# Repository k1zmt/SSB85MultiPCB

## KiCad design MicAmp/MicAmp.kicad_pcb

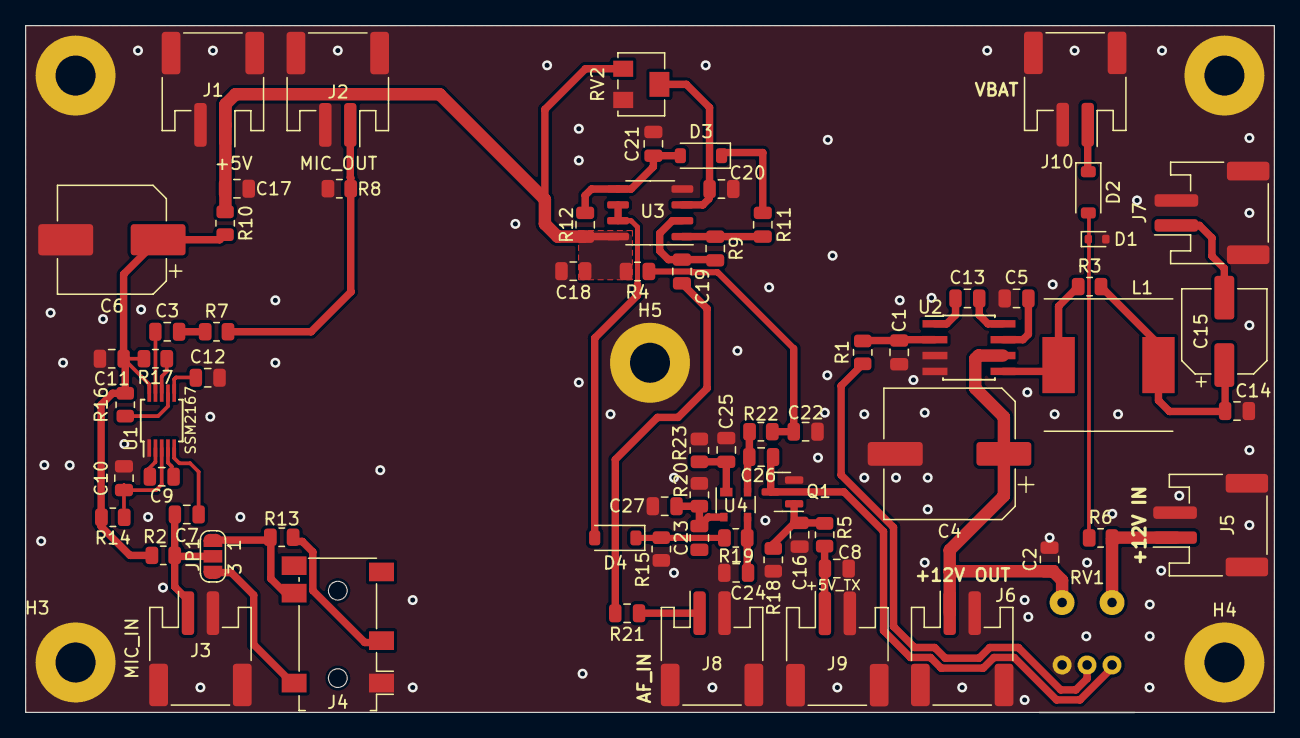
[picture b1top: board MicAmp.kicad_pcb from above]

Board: 2 copper layers, 100.0 x 55.0 mm, 78 parts (0 on the bottom side), 46 nets.

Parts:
C1: 222; C_0805_2012Metric
C2, C3, C5, C9, C12, C13, C22, C25, C26: 106; C_0805_2012Metric
C4: 1000uFx16V; CP_Elec_10x12.6
C6: 100uFx6.3V; CP_Elec_8x10.5
C7, C8, C10, C11, C16, C17, C18, C19, C20, C24, C27: 104; C_0805_2012Metric
C14: 473; C_0805_2012Metric
C15: 227; CP_Elec_6.3x3
C21, C23: 105; C_0805_2012Metric
D1: DZ2S036X0L; D_SOD-523
D2: 1N4148; D_SOD-123
D3, D4: MBR0520; D_SOD-123
H1, H2, H3, H4, H5: MH; MountingHole_3.2mm_M3_Pad
J1: +5V; JST_PH_S2B-PH-SM4-TB_1x02-1MP_P2.00mm_Horizontal
J2: MIC_OUT; JST_PH_S2B-PH-SM4-TB_1x02-1MP_P2.00mm_Horizontal
J3: MIC_IN; JST_PH_S2B-PH-SM4-TB_1x02-1MP_P2.00mm_Horizontal
J4: AudioJack3_Ground_SwitchTR; Jack_3.5mm_PJ342_Horizontal2
J5: +12V IN; JST_PH_S2B-PH-SM4-TB_1x02-1MP_P2.00mm_Horizontal
J6: +12V OUT; JST_PH_S2B-PH-SM4-TB_1x02-1MP_P2.00mm_Horizontal
J7: SPEAKER; JST_PH_S2B-PH-SM4-TB_1x02-1MP_P2.00mm_Horizontal
J8: AF_IN; JST_PH_S2B-PH-SM4-TB_1x02-1MP_P2.00mm_Horizontal
J9: +5V_TX; JST_PH_S2B-PH-SM4-TB_1x02-1MP_P2.00mm_Horizontal
J10: VBAT; JST_PH_S2B-PH-SM4-TB_1x02-1MP_P2.00mm_Horizontal
JP1: MIC; SolderJumper-3_P1.3mm_Open_RoundedPad1.0x1.5mm_NumberLabels
L1: L_Ferrite; L_Taiyo-Yuden_NR-10050_9.8x10.0mm
Q1: BSS123; SOT-23
R1, R2, R5, R14, R15, R18, R19: 103; R_0805_2012Metric
R3, R10: 47R; R_0805_2012Metric
R4: 510; R_0805_2012Metric
R6: 106; R_0805_2012Metric
R7, R8: 472; R_0805_2012Metric
R9: 104; C_0805_2012Metric
R11, R21: 102; C_0805_2012Metric
R12: 105; C_0805_2012Metric
R13, R20: 101; R_0805_2012Metric
R16: 202; R_0805_2012Metric
R17: 473; R_0805_2012Metric
R22: 681; R_0805_2012Metric
R23: 221; R_0805_2012Metric
RV1: A10K; Potentiometer_Switch
RV2: 503; Potentiometer_Bourns_3224W_Vertical
U1: SSM2167; MSOP-10_3x3mm_P0.5mm
U2: LM386; PowerIntegrations_SO-8
U3: LM358; SO-8_3.9x4.9mm_P1.27mm
U4: BF998R; SOT-143R

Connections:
+5V: C17.1, C18.2, J1.1, R4.2, R10.1, R12.2, RV2.1, U3.8 (V+)
+12V: C2.2, C4.1, J6.1, RV1.5 (S1), U2.6 (V+)
/+5V_MIC_COMP: C6.1, C11.1, R2.1, R10.2, R14.2, R16.1, R17.1, U1.10 (V+)
/+12V_IN: J5.1, R6.2, RV1.4 (S2)
/AF_AGC_OUT: C26.2, Q1.3 (D), RV1.3
/AUDIO_IN: C23.1, J8.1, R21.1
/MIC: C7.2, J3.1, JP1.2 (C), R2.2
/MIC_OUT: J2.1, R7.2, R8.2
/SPK: C15.2, J7.1
/VBAT: D2.1 (K), J10.1
Earth: C1.2, C2.1, C4.2, C5.1, C6.2, C8.2, C10.1, C11.2, C12.2, C14.2, C16.2, C17.2, C18.1, C20.1, C21.1, C22.1, C24.1, C25.1, C27.1, D1.2 (A), H1.1, H2.1, H3.1, H4.1, H5.1, J1.2, J1.MP (MountPin), J2.2, J2.MP (MountPin), J3.2, J3.MP (MountPin), J4.G, J5.2, J5.MP (MountPin), J6.2, J6.MP (MountPin), J7.2, J7.MP (MountPin), J8.2, J8.MP (MountPin), J9.2, J9.MP (MountPin), J10.2, J10.MP (MountPin), Q1.2 (S), R8.1, R15.2, R18.1, R20.2, R23.2, RV1.1, RV2.3, U1.1 (GND), U2.3 (+), U2.4 (GND), U3.4 (V-)
unnamed: C3.2, R7.1
unnamed: C13.1, U2.1 (GAIN)
unnamed: C13.2, U2.8 (GAIN)
unnamed: C14.1, C15.1, L1.2, R3.2
unnamed: C19.1, R21.2
unnamed: C22.2, R4.1, R22.1
unnamed: D1.1 (K), D2.2 (A), R6.1
unnamed: C21.2, D3.2 (A), R12.1, U3.5 (+)
unnamed: D3.1 (K), R11.2
unnamed: D4.2 (A), U3.6 (-), U3.7
unnamed: D4.1 (K), R15.1, R19.1
unnamed: J4.R, R13.1
unnamed: J4.T, JP1.1 (A), R13.2
unnamed: J4.S, JP1.3 (B)
unnamed: L1.1, R3.1, U2.5
unnamed: C16.1, Q1.1 (G), R5.2, R18.2
unnamed: R1.1, RV1.2
unnamed: R9.2, R11.1, U3.1
unnamed: C12.1, U1.6 (AVG)
unnamed: C9.1, U1.4 (BUFOUT)
unnamed: R17.2, U1.8 (COMP)
unnamed: R16.2, U1.7 (GATE)
unnamed: C7.1, U1.5 (IN+)
unnamed: C9.2, U1.2 (VCAIN)
unnamed: C3.1, U1.9 (VOUT)
unnamed: C10.2, R14.1, U1.3 (~SD)
unnamed: C1.1, R1.2, U2.2 (-)
unnamed: C5.2, U2.7 (BYPASS)
unnamed: C20.2, RV2.2, U3.3 (+)
unnamed: C19.2, R9.1, U3.2 (-)
unnamed: C26.1, R22.2, U4.2 (D)
unnamed: C23.2, C27.2, R20.1, U4.4 (G1)
unnamed: C24.2, R19.2, U4.3 (G2)
unnamed: C25.2, R23.1, U4.1 (S)
TX+5V: C8.1, J9.1, R5.1

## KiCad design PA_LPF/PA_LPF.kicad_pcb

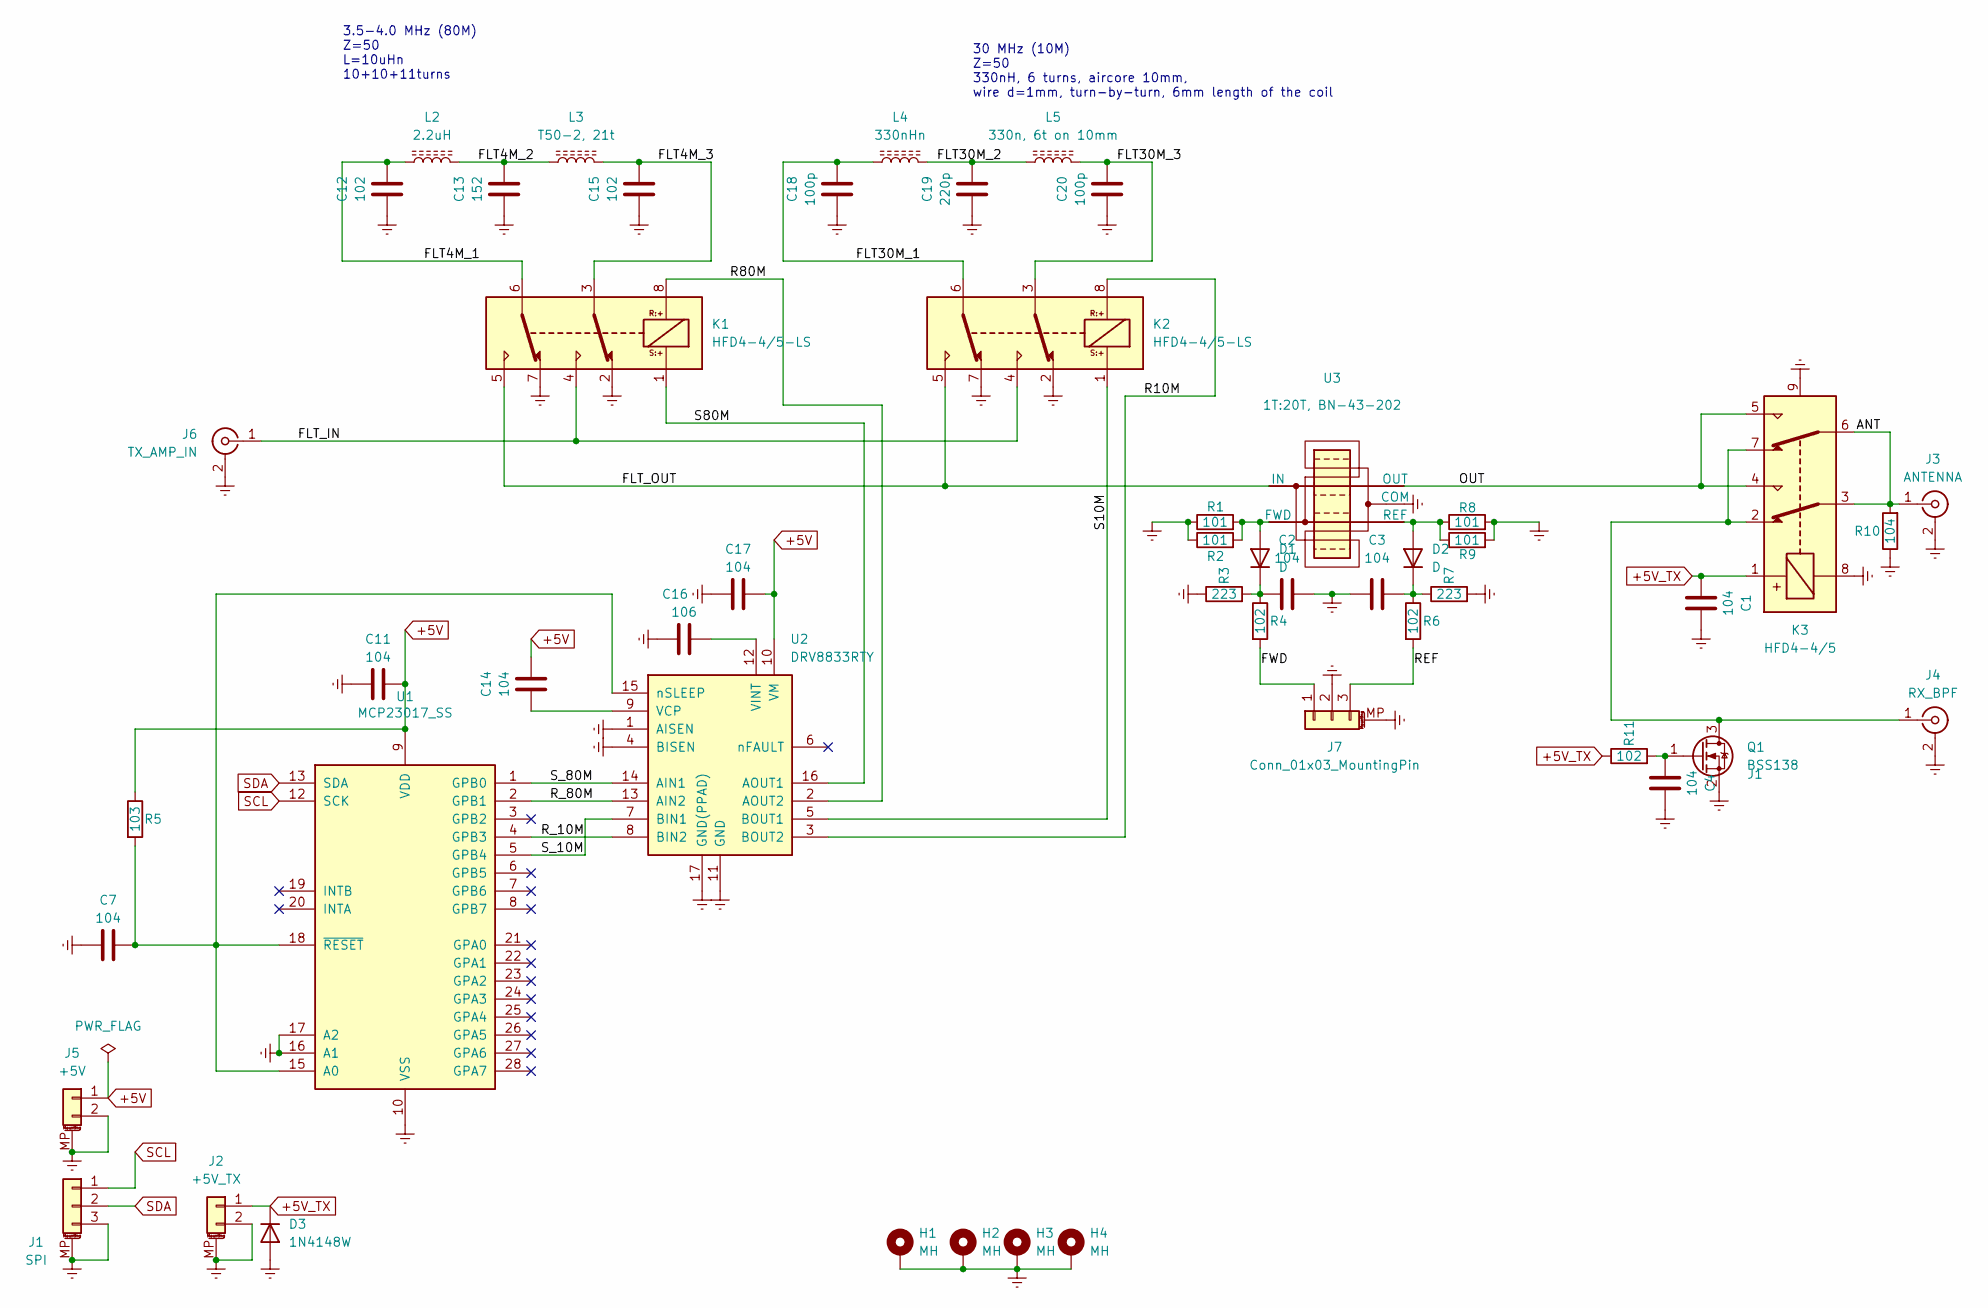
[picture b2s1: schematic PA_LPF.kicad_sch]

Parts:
C1, C2, C3, C4, C7, C11, C14, C17: 104; C_0805_2012Metric
C12, C15: 102; C_1206_3216Metric
C13: 152; C_1206_3216Metric
C16: 106; C_0805_2012Metric
C18, C20: 100p; C_1206_3216Metric
C19: 220p; C_1206_3216Metric
D1, D2: D; D_SOD-123
D3: 1N4148W; D_SOD-123
H1, H2, H3, H4: MH; MountingHole_3.2mm_M3_Pad
J1: SPI; JST_PH_S3B-PH-SM4-TB_1x03-1MP_P2.00mm_Horizontal
J2: +5V_TX; JST_PH_S2B-PH-SM4-TB_1x02-1MP_P2.00mm_Horizontal
J3: ANTENNA; SMA_Amphenol_132289_EdgeMount
J4: RX_BPF; SMA_Amphenol_132289_EdgeMount
J5: +5V; JST_PH_S2B-PH-SM4-TB_1x02-1MP_P2.00mm_Horizontal
J6: TX_AMP_IN; SMA_Samtec_SMA-J-P-X-ST-EM1_EdgeMount
J7: Conn_01x03_MountingPin; JST_PH_S3B-PH-SM4-TB_1x03-1MP_P2.00mm_Horizontal
K1, K2: HFD4-4/5-LS; Relay_DPDT_Omron_G6K-2F-Y
K3: HFD4-4/5; Relay_DPDT_Omron_G6K-2F-Y
L2: 2.2uH; L_T50_L13_W8_P5mm
L3: T50-2, 21t; L_T50_L13_W8_P5mm
L4: 330nHn; L_T50_L13_W8_P5mm
L5: 330n, 6t on 10mm; L_T50_L13_W8_P5mm
Q1: BSS138; SOT-23
R1, R2, R8, R9: 101; R_1812_4532Metric
R3, R7: 223; R_0805_2012Metric
R4, R6, R11: 102; R_0805_2012Metric
R5: 103; R_0805_2012Metric
R10: 104; R_0805_2012Metric
U1: MCP23017_SS; SSOP-28_5.3x10.2mm_P0.65mm
U2: DRV8833RTY; Texas_S-PWQFN-N16_EP2.1x2.1mm_ThermalVias
U3: 1T:20T, BN-43-202; Balun_5PIN_BN-43-202_SMD_SWR_Bridge

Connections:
+5V: C11.1, C14.2, C17.2, J5.1, R5.1, U1.9 (VDD), U2.10 (VM)
+5V_TX: C1.1, D3.1 (K), J2.1, K3.1, R11.1
/ANT: J3.1 (In), K3.3, K3.6, R10.2
/FLT4M_1: C12.2, K1.6, L2.1
/FLT4M_2: C13.2, L2.2, L3.1
/FLT4M_3: C15.2, K1.3, L3.2
/FLT30M_1: C18.2, K2.6, L4.1
/FLT30M_2: C19.2, L4.2, L5.1
/FLT30M_3: C20.2, K2.3, L5.2
/FLT_IN: J6.1 (In), K1.4, K2.4
/FLT_OUT: K1.5, K2.5, U3.1 (IN)
/FWD: J7.1, R4.2
/OUT: K3.4, K3.5, U3.2 (OUT)
/R10M: K2.8, U2.3 (BOUT2)
/R80M: K1.8, U2.2 (AOUT2)
/REF: J7.3, R6.2
/R_10M: U1.4 (GPB3), U2.8 (BIN2)
/R_80M: U1.2 (GPB1), U2.13 (AIN2)
/S10M: K2.1, U2.5 (BOUT1)
/S80M: K1.1, U2.16 (AOUT1)
/S_10M: U1.5 (GPB4), U2.7 (BIN1)
/S_80M: U1.1 (GPB0), U2.14 (AIN1)
Earth: C1.2, C2.2, C3.1, C4.2, C7.1, C11.2, C12.1, C13.1, C15.1, C16.1, C17.1, C18.1, C19.1, C20.1, D3.2 (A), H1.1, H2.1, H3.1, H4.1, J1.3, J1.MP (MountPin), J2.2, J2.MP (MountPin), J3.2 (Ext), J4.2 (Ext), J5.2, J5.MP (MountPin), J6.2 (Ext), J7.2, J7.MP (MountPin), K1.2, K1.7, K2.2, K2.7, K3.8, K3.9, Q1.2 (S), R1.1, R2.1, R3.1, R7.2, R8.2, R9.2, R10.1, U1.10 (VSS), U1.16 (A1), U1.17 (A2), U2.1 (AISEN), U2.4 (BISEN), U2.11 (GND), U2.17 (GND(PPAD)), U3.3 (COM)
unnamed: D1.2 (A), R1.2, R2.2, U3.5 (FWD)
unnamed: C2.1, D1.1 (K), R3.2, R4.1
unnamed: D2.2 (A), R8.1, R9.1, U3.4 (REF)
unnamed: C3.2, D2.1 (K), R6.1, R7.1
unnamed: J4.1 (In), K3.2, K3.7, Q1.3 (D)
unnamed: C4.1, Q1.1 (G), R11.2
unnamed: C7.2, R5.2, U1.15 (A0), U1.18 (~RESET), U2.15 (nSLEEP)
unnamed: C14.1, U2.9 (VCP)
unnamed: C16.2, U2.12 (VINT)
SCL: J1.1, U1.12 (SCK)
SDA: J1.2, U1.13 (SDA)

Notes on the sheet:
3.5-4.0 MHz (80M) Z=50 L=10uHn 10+10+11turns
30 MHz (10M) Z=50 330nH, 6 turns, aircore 10mm, wire d=1mm, turn-by-turn, 6mm length of the coil

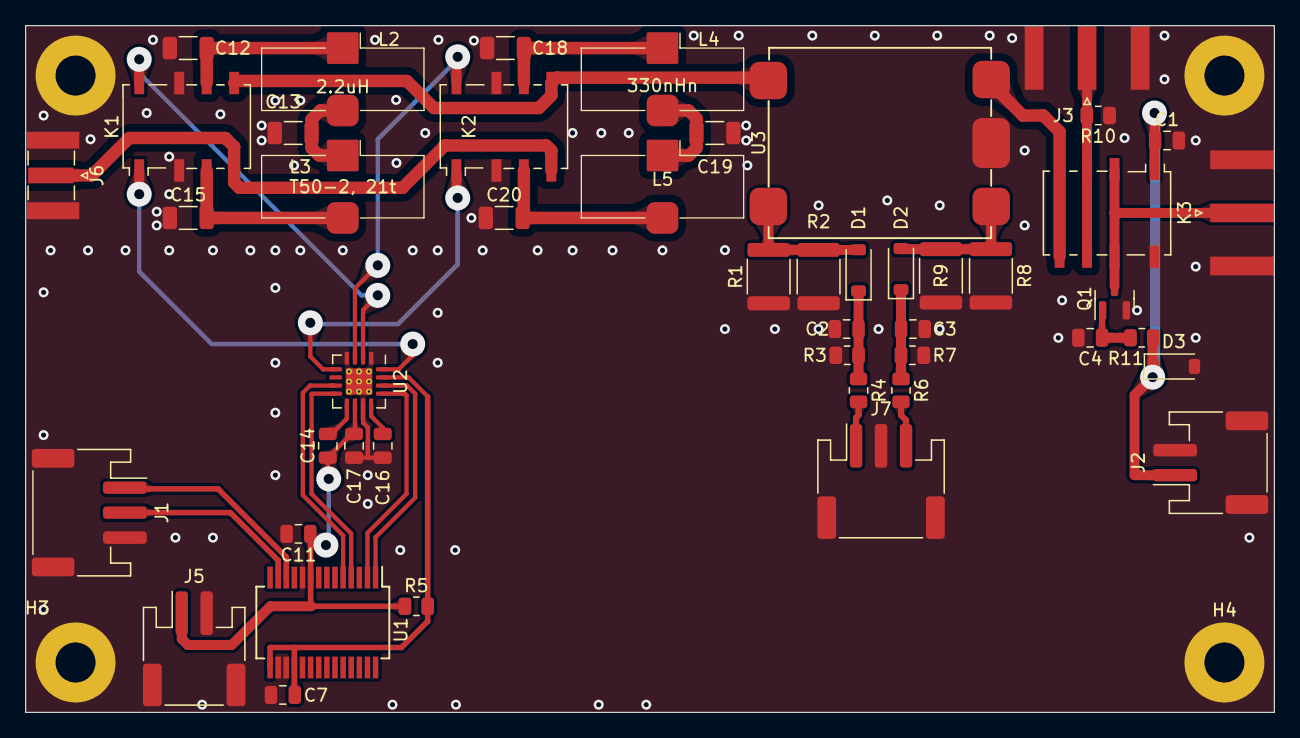
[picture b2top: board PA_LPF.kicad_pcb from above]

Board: 2 copper layers, 100.0 x 55.0 mm, 51 parts (0 on the bottom side), 34 nets.

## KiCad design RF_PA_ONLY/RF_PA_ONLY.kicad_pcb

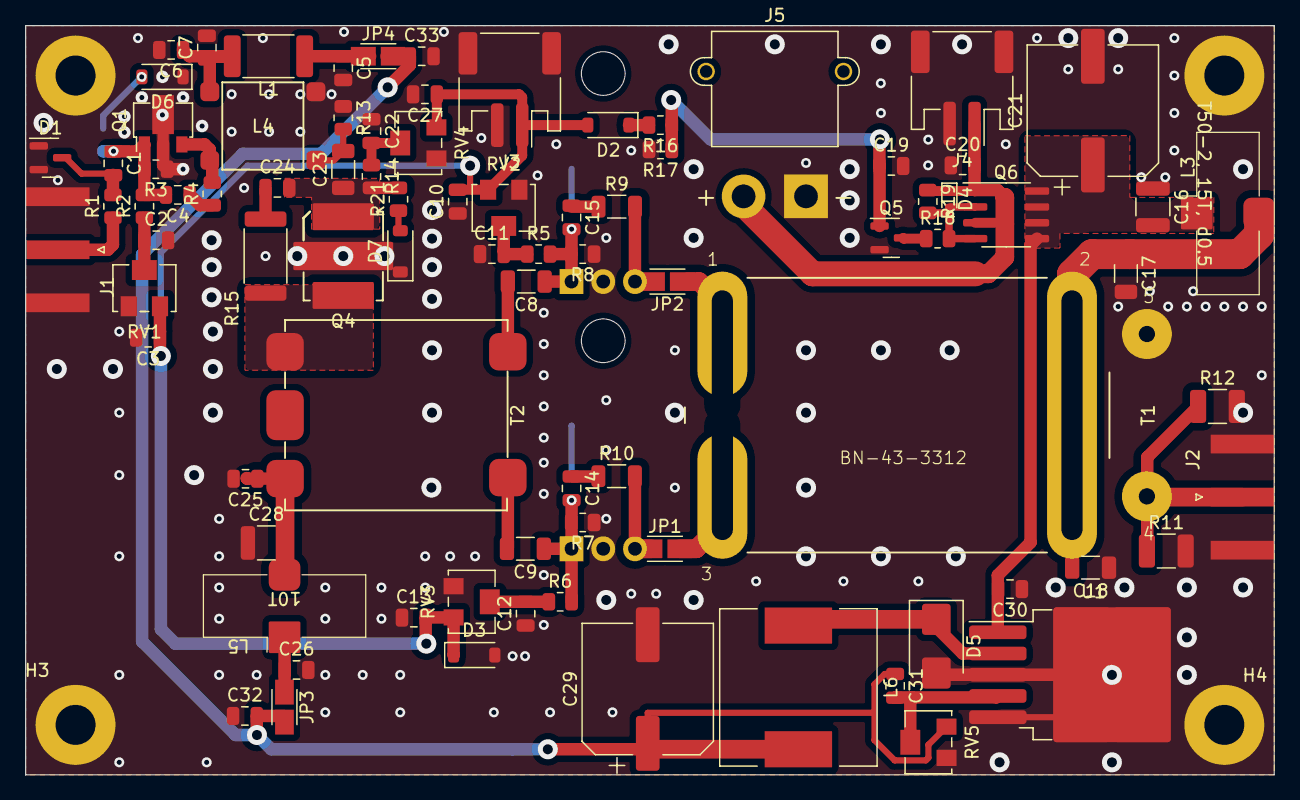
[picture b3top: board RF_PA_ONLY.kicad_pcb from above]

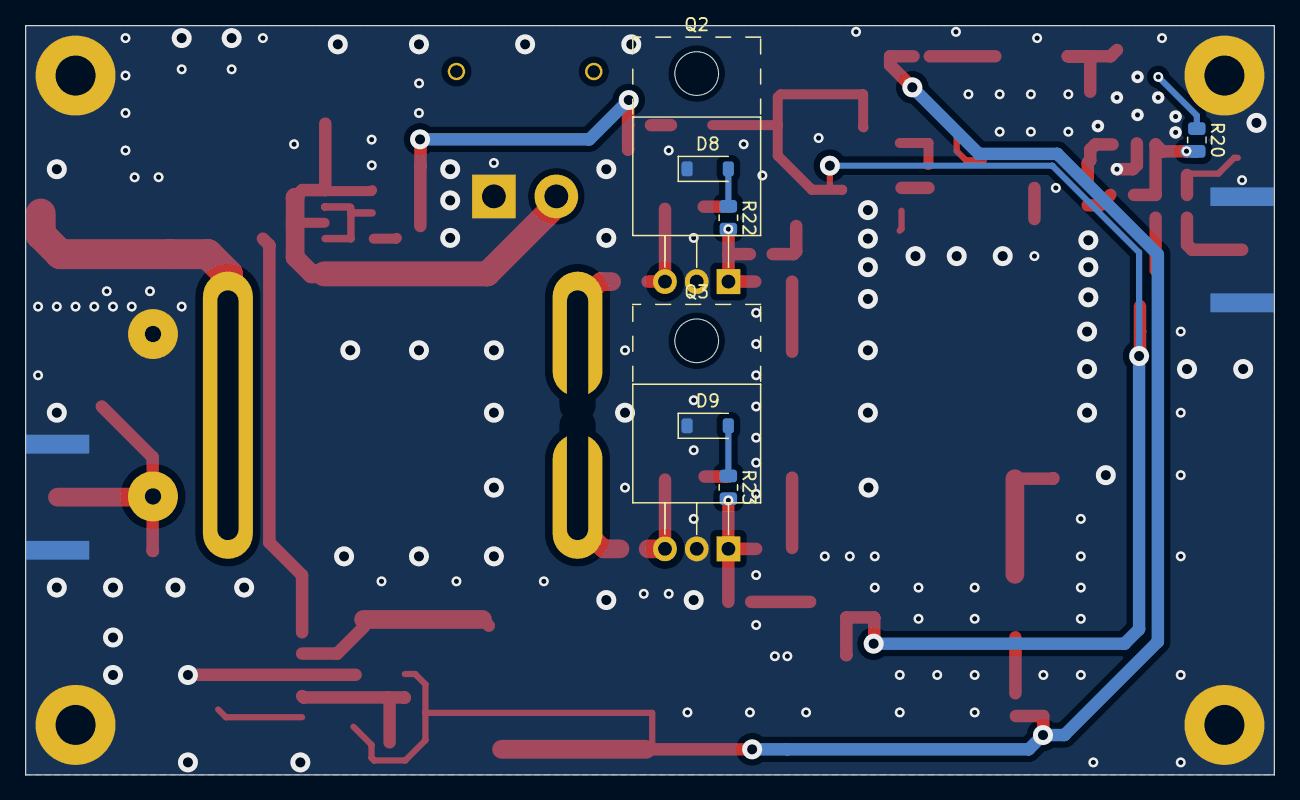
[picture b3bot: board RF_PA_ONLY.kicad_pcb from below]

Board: 2 copper layers, 100.0 x 60.0 mm, 97 parts (7 on the bottom side), 44 nets.

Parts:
C1, C2, C3, C5, C6, C7, C10, C11, C12, C13, C20, C22, C25, C26, C27, C30, C31, C32, C33: 104; C_0805_2012Metric
C4: 103; C_0805_2012Metric
C8, C9, C17, C18, C23: 104; C_1206_3216Metric
C14, C15: 223; C_0805_2012Metric
C16: 104; C_1210_3225Metric
C19: 106; C_0805_2012Metric
C21, C29: 1000uFx16V; CP_Elec_10x12.6
C24: 473; C_0805_2012Metric
C28: 102; C_1210_3225Metric
D1: BAV99; SOT-23
D2, D3, D6, D7, D8, D9: 1N4148W; D_SOD-123
D4: DZ2S100X0L; D_SOD-523
D5: D_Schottky; D_SMB
H1, H2, H3, H4: MH; MountingHole_3.2mm_M3_Pad
J1, J2: TX_IN; SMA_Amphenol_132289_EdgeMount
J3: +5V_TX; JST_PH_S2B-PH-SM4-TB_1x02-1MP_P2.00mm_Horizontal
J4: +12V OUT; JST_PH_S2B-PH-SM4-TB_1x02-1MP_P2.00mm_Horizontal
J5: XT30PW-M; AMASS_XT30PW-M_1x02_P2.50mm_Horizontal
JP1, JP2, JP3, JP4: SJ; SolderJumper-2_P1.3mm_Open_Pad2.0x1.5mm
L1: 10T; L_2512_6332Metric
L3: T50-2, 15T, d0.5; L_T50_L13_W8_P5mm
L4: 2T:1T; Balun_BN-43-2402_SMD
L5: 10T; L_T50_L13_W8_P5mm
L6: 10T; L_12x12mm_H8mm
Q1: RD01MUS2B; SOT-89-3
Q2, Q3: RD16HHF1; TO-220-3_Horizontal_TabUp
Q4: AFT09MS007NT1; PLD-1.5W-NoVias
Q5: BSS138; SOT-23
Q6: IRF7324; SOIC-8_3.9x4.9mm_P1.27mm
R1: 47R; R_0805_2012Metric
R2, R3, R7, R8, R14, R20, R21, R22, R23: 472; R_0805_2012Metric
R4, R18: 102; R_0805_2012Metric
R5, R6: 331; R_0805_2012Metric
R9, R10: 751; R_1206_3216Metric
R11, R12: 511; R_1210_3225Metric_Pad1.30x2.65mm_HandSolder
R13: 22R; R_0805_2012Metric
R15: 102; R_2512_6332Metric
R16, R19: 103; R_0805_2012Metric
R17: 475; R_0805_2012Metric
RV1, RV2, RV3, RV5: 502; Potentiometer_Bourns_3214W_Vertical
RV4: 502; Potentiometer_Bourns_3224W_Vertical
T1: 0.5+0.5T:4T; Transformer_BN-43-3312
T2: 2T:4T; Balun_5PIN_BN-43-202_SMD_Inverse
U1: LM2596S-ADJ; TO-263-5_TabPin3

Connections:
+5V_TX: C3.1, C10.2, C13.2, C27.1, D2.2 (A), D3.1 (K), J3.1, RV1.3, RV2.3, RV3.3, RV4.3
+7V_TX: C29.1, C31.1, C32.2, C33.1, JP3.2 (B), JP4.2 (B), L6.2, RV5.3
+12V: C20.2, D4.1 (K), J4.1, J5.2, Q6.1 (S1), Q6.3 (S2), R19.1
+12V_TX: C16.2, C21.1, C30.2, L3.1, Q6.5 (D2), Q6.6 (D2), Q6.7 (D1), Q6.8 (D1), U1.1 (VIN)
/DRN_1: JP2.2 (B), Q2.3 (D), R9.2
/DRN_2: JP1.1 (A), Q3.3 (D), R10.2
/DRN_T: C17.1, C18.2, L3.2, T1.2 (PM)
/DRN_T1: JP2.1 (A), T1.1 (PR1)
/DRN_T2: JP1.2 (B), T1.3 (PR2)
/FLT_IN: J2.1 (In), R11.1, R12.1, T1.4 (S1)
/P_D: Q4.1 (D), R15.1, T2.5 (S2)
/P_DT: C25.1, C28.2, L5.2, T2.4 (S1)
/P_G: C23.1, C24.2, Q4.2 (G), R14.2, R21.2
Earth: C2.2, C3.2, C5.2, C6.2, C7.2, C10.1, C11.1, C12.1, C13.1, C16.1, C17.2, C18.1, C19.2, C20.1, C21.2, C22.1, C25.2, C26.2, C27.2, C28.1, C29.2, C30.1, C32.1, C33.2, D1.1 (K), D1.2 (A), D3.2 (A), D5.2 (A), D6.1 (K), D7.1 (K), D8.1 (K), D9.1 (K), H1.1, H2.1, H3.1, H4.1, J1.2 (Ext), J2.2 (Ext), J3.2, J3.MP (MountPin), J4.2, J4.MP (MountPin), J5.1, L4.4, Q1.2 (S), Q2.2 (S), Q3.2 (S), Q4.3 (S), Q5.2 (S), R3.1, R7.1, R8.1, R11.2, R12.2, R13.1, R17.2, RV1.1, RV2.1, RV3.1, RV4.1, RV5.1, T1.5 (S2), U1.3 (GND), U1.5 (~ON/OFF)
unnamed: C1.2, D1.3 (K), R1.2
unnamed: C2.1, R2.1, RV1.2
unnamed: C4.1, R4.1
unnamed: C6.1, C7.1, L1.2, L4.1
unnamed: C11.2, R5.1, RV2.2
unnamed: C12.2, R6.1, RV3.2
unnamed: C14.1, R10.1
unnamed: C15.1, R9.1
unnamed: C22.2, R14.1, RV4.2
unnamed: C23.2, L4.3, R13.2
unnamed: C24.1, R15.2
unnamed: D2.1 (K), R16.2
unnamed: D4.2 (A), Q6.2 (G1), Q6.4 (G2), R18.2, R19.2
unnamed: D5.1 (K), L6.1, U1.2 (OUT)
unnamed: D6.2 (A), R20.1
unnamed: D7.2 (A), R21.1
unnamed: D8.2 (A), R22.1
unnamed: D9.2 (A), R23.1
unnamed: J1.1 (In), R1.1
unnamed: C26.1, JP3.1 (A), L5.1
unnamed: C5.1, JP4.1 (A), L1.1
unnamed: L4.2, Q1.3 (D), R4.2
unnamed: C1.1, C4.2, Q1.1 (G), R2.2, R3.2, R20.2
unnamed: C8.1, C15.2, Q2.1 (G), R5.2, R8.2, R22.2
unnamed: C9.1, C14.2, Q3.1 (G), R6.2, R7.2, R23.2
unnamed: Q5.3 (D), R18.1
unnamed: C19.1, Q5.1 (G), R16.1, R17.1
unnamed: C8.2, T2.1 (PR1)
unnamed: C9.2, T2.3 (PR2)
unnamed: C31.2, RV5.2, U1.4 (FB)
